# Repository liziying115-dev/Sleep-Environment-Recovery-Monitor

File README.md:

## Sleep Environment & Recovery Monitor
### Project Overview
#### What it does

The Sleep Environment & Recovery Monitor evaluates overnight sleep conditions — light, sound, temperature — and translates them into a simple, physical recovery score visible in the morning. Instead of tracking the body, the system focuses on environmental quality to encourage healthier sleep habits without medical claims.

#### What it looks like

The system consists of two devices:
* A sensor unit placed on a nightstand that quietly monitors the sleep environment overnight (light, sound, temperature)
* A display unit resembling a small alarm clock with an OLED screen, LED indicator, and a stepper-motor-driven gauge needle that physically points to your sleep quality score

### Sensor Device (Sleep Environment Monitor)
#### Description
The sensor device continuously monitors environmental conditions during sleep using a low-power duty cycle. Data is aggregated overnight and transmitted wirelessly to the display device in the morning.

#### Sensors & Parts (part numbers)
| Function | Part Number | Quantity | Description |
|---------|------------|----------|-------------|
| MCU + Wireless| Seeed Studio XIAO ESP32-C3| 1 | BLE, low power |
| Ambient Light Sensor | VEML7700 | 1 | High-sensitivity ambient light sensor (I²C) |
| Microphone | SPH0645LM4H-B | 1 | I²S MEMS microphone, RMS only |
| Temperature | BME280 | 1 | temperature sensing |
| Battery Charger | MCP73831 | 1 | LiPo charging IC |
| LiPo Battery | 3.7V 1000-2000mAh | 1 | Power supply |

#### How it works
- The device wakes on a scheduled interval during sleep hours.
- Light, sound RMS, temperature are sampled.
- Audio is processed locally (no recording or storage).
- All data is time-weighted and stored in local memory.
- At wake time, a summary packet is transmitted to the display device.

### Display Device (Score Interface)
#### Description
The display device receives environmental data wirelessly and presents the overnight Sleep Environment Score using multiple feedback channels: a physical gauge needle, OLED screen, and ambient LED indicator. A single button allows the user to cycle through secondary metrics such as light exposure, noise level, and temperature.

#### Components & Parts
| Function | Part Number | Quantity | Notes |
|---------|------------|----------|------|
| MCU + Wireless | Seeed Studio XIAO ESP32-C3 | 1 | Wireless receiver |
| Display | SSD1306 OLED (128×64) | 1 | Low-power I²C screen |
| Stepper Motor | 28BYJ-48 (5V)        | 1 | Drives gauge needle        |
| Motor Driver  | ULN2003 Driver Board | 1 | Stepper motor driver       |
| Gauge Needle  | Custom (3D printed)  | 1 | Physical pointer (0-100)   |
| LED | Warm White Diffused LED | 1 | Ambient sleep quality indicator |
| Button | Tactile Momentary Switch | 1 | Metric navigation |
| Battery | LiPo 2000 mAh | 1 | Multi-day operation |
| Resistor | 220Ω | 1 | LED current limiting |

#### Gauge Needle Design

Scale: 0-100 (semi-circular arc)

Zones:
- 0-50: Red zone (Poor)
- 50-70: Orange zone (Fair)
- 70-90: Yellow zone (Good)
- 90-100: Green zone (Excellent)

### System Communication & Data Flow

*Figure: Complete data pipeline from sensors through processing to display outputs.*

#### System Communication
The system consists of two standalone devices that communicate wirelessly:

Sensor Unit (Transmitter):
- Operates independently overnight
- Collects and aggregates environmental data
- Transmits single summary packet in the morning

Display Unit (Receiver):
- Listens for BLE transmission from sensor unit
- Receives aggregated data and calculated score
- Updates three output channels: gauge needle, OLED, LED

Communication Protocol:
- Technology: BLE
- Pairing: One-time setup, devices remember each other
- Data Format: JSON or binary packet containing:
  - Overall score (0-100)
  - Average light level (lux)
  - Average sound level (dB RMS)
  - Average temperature (°F/°C)
  - Timestamp

#### Data Flow & Processing Pipeline

During Sleep Period:
1. Sensor device periodically samples ambient light, sound level, and temperature
2. Audio data is processed locally using RMS calculation and basic spectral weighting to emphasize disruptive noise patterns
3. All sensor readings are time-weighted (e.g., disruptions during REM sleep weighted higher)
4. Data is aggregated into a single overnight dataset

Morning Transmission:
1. Aggregated data is converted into a normalized Sleep Environment Score (0-100)
2. Score and detailed metrics are packaged into BLE transmission packet
3. Sensor unit broadcasts packet to display unit
4. Display unit receives data and updates all feedback channels

Physical Feedback:
- Gauge Needle: Stepper motor positions needle to corresponding score (0-100 scale)
- OLED Screen: Displays numeric score and allows cycling through detailed metrics
- LED Indicator: Glows with color corresponding to quality zone (green/yellow/orange/red)

### Future Work
- Optional Wi-Fi connectivity to support long-term data logging or remote visualization

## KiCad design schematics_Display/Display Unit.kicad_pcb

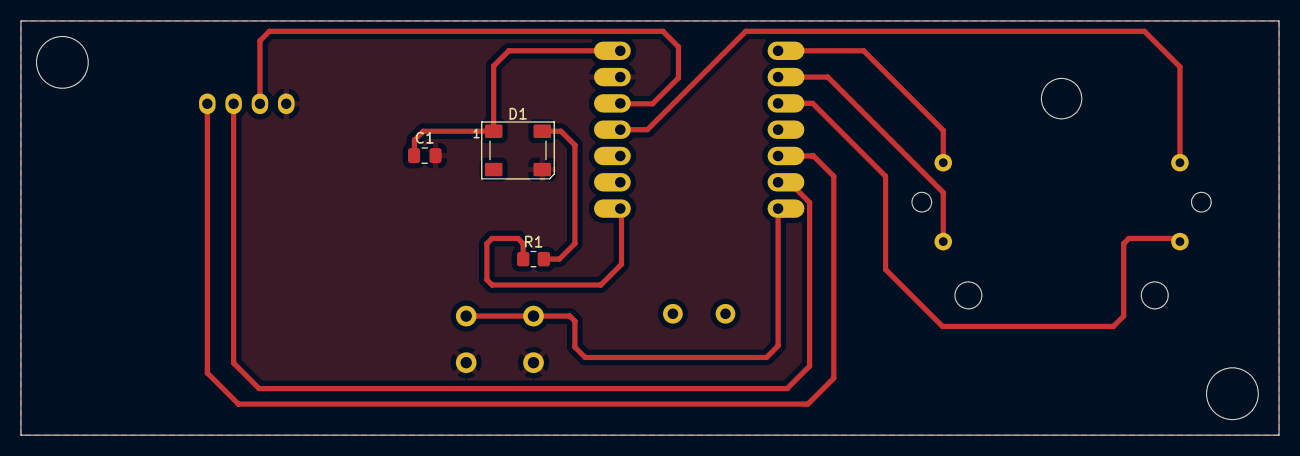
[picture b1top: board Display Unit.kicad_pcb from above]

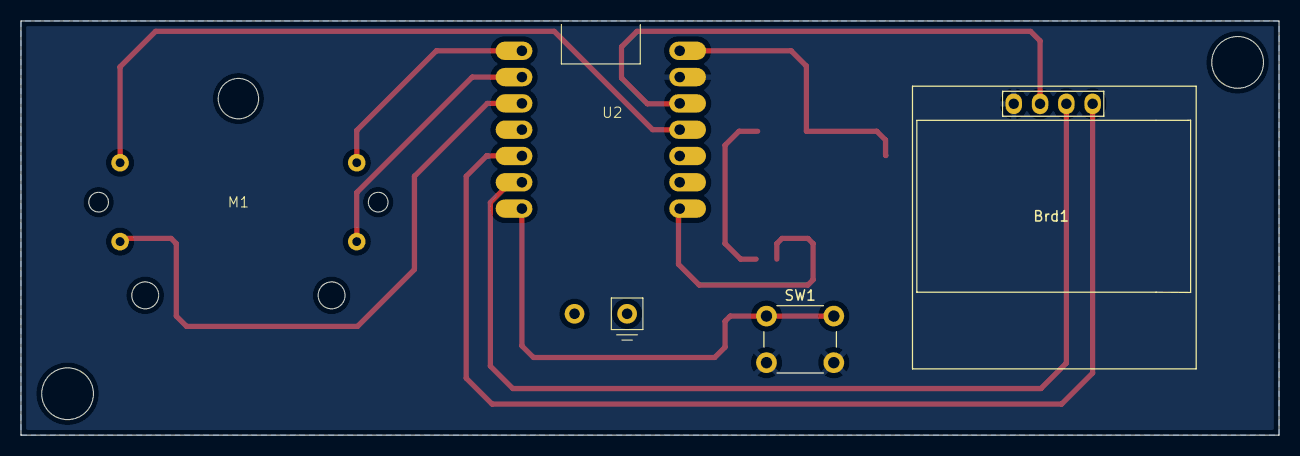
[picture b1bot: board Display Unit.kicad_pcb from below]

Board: 2 copper layers, 121.5 x 40.0 mm, 7 parts (4 on the bottom side), 12 nets.

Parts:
Brd1: SSD1306; 128x64OLED
C1: 100nF; C_0805_2012Metric_Pad1.18x1.45mm_HandSolder
D1: WS2812B; LED_WS2812B_PLCC4_5.0x5.0mm_P3.2mm
M1: Stepper_Motor_bipolar; x27_stepper_two_holes
R1: 33Ω; R_0805_2012Metric_Pad1.20x1.40mm_HandSolder
SW1: SW_Push; SW_PUSH_6mm_H4.3mm
U2: XIAO_ESP32C3; XIAO_ESP32

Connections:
GND: Brd1.1 (GND), C1.2, D1.3 (VSS), SW1.2, U2.13 (GND)
unnamed: Brd1.3 (SCL), U2.6 (GPIO6_A5_D5_SCL)
unnamed: Brd1.4 (SDA), U2.5 (GPIO4_A3_D3_SDA)
unnamed: Brd1.2 (VCC), U2.12 (3V3)
unnamed: D1.4 (DIN), R1.2
unnamed: C1.1, D1.1 (VDD), U2.14 (5V)
unnamed: M1.2 (-), U2.2 (GPIO2_A1_D1)
unnamed: M1.1, U2.1 (GPIO1_A0_D0)
unnamed: M1.4, U2.3 (GPIO3_A2_D2)
unnamed: M1.3, U2.11 (GPIO9_A10_D10_COPI)
unnamed: SW1.1, U2.7 (GPIO43_TX_D6)
unnamed: R1.1, U2.8 (GPIO44_D7_RX)

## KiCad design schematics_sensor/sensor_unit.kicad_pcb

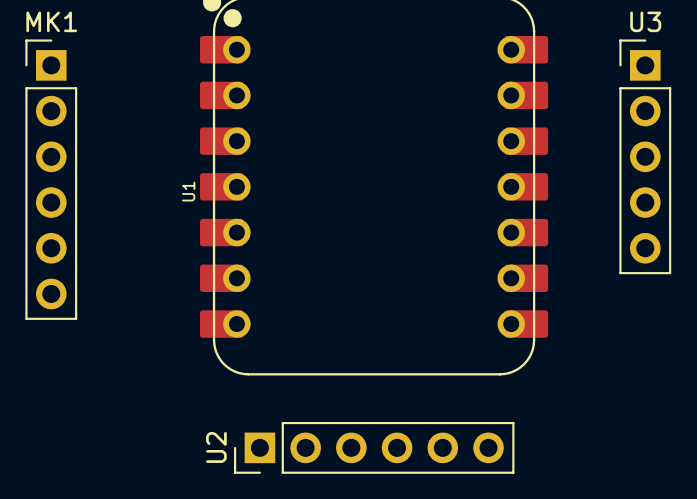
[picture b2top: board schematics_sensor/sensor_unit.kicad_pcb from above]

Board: 2 copper layers, 4 parts (0 on the bottom side), 7 nets, no tracks yet.

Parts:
MK1: SPH0645LM4H; PinHeader_1x06_P2.54mm_Vertical
U1: XIAO ESP32C3; XIAO-ESP32-C3-DIP
U2: BMP280; PinHeader_1x06_P2.54mm_Vertical
U3: VEML7700; PinHeader_1x05_P2.54mm_Vertical

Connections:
unnamed: MK1.5 (3V), U1.12 (3V3), U2.2 (CSB), U2.6 (VDDIO), U3.1 (VIN)
unnamed: MK1.4 (BCLK), U1.2 (GPIO2_A1_D1)
unnamed: MK1.6 (DOUT), U1.3 (GPIO3_A2_D2)
unnamed: MK1.2 (SEL), MK1.3 (GND), U1.13 (GND), U2.1 (GND), U2.5 (SDO), U3.3 (GND)
unnamed: MK1.1 (LRCL), U1.1 (GPIO1_A0_D0)
unnamed: U1.5 (GPIO4_A3_D3_SDA), U2.3 (SDI), U3.5 (SDA)
unnamed: U1.6 (GPIO6_A5_D5_SCL), U2.4 (SCK), U3.4 (SCL)

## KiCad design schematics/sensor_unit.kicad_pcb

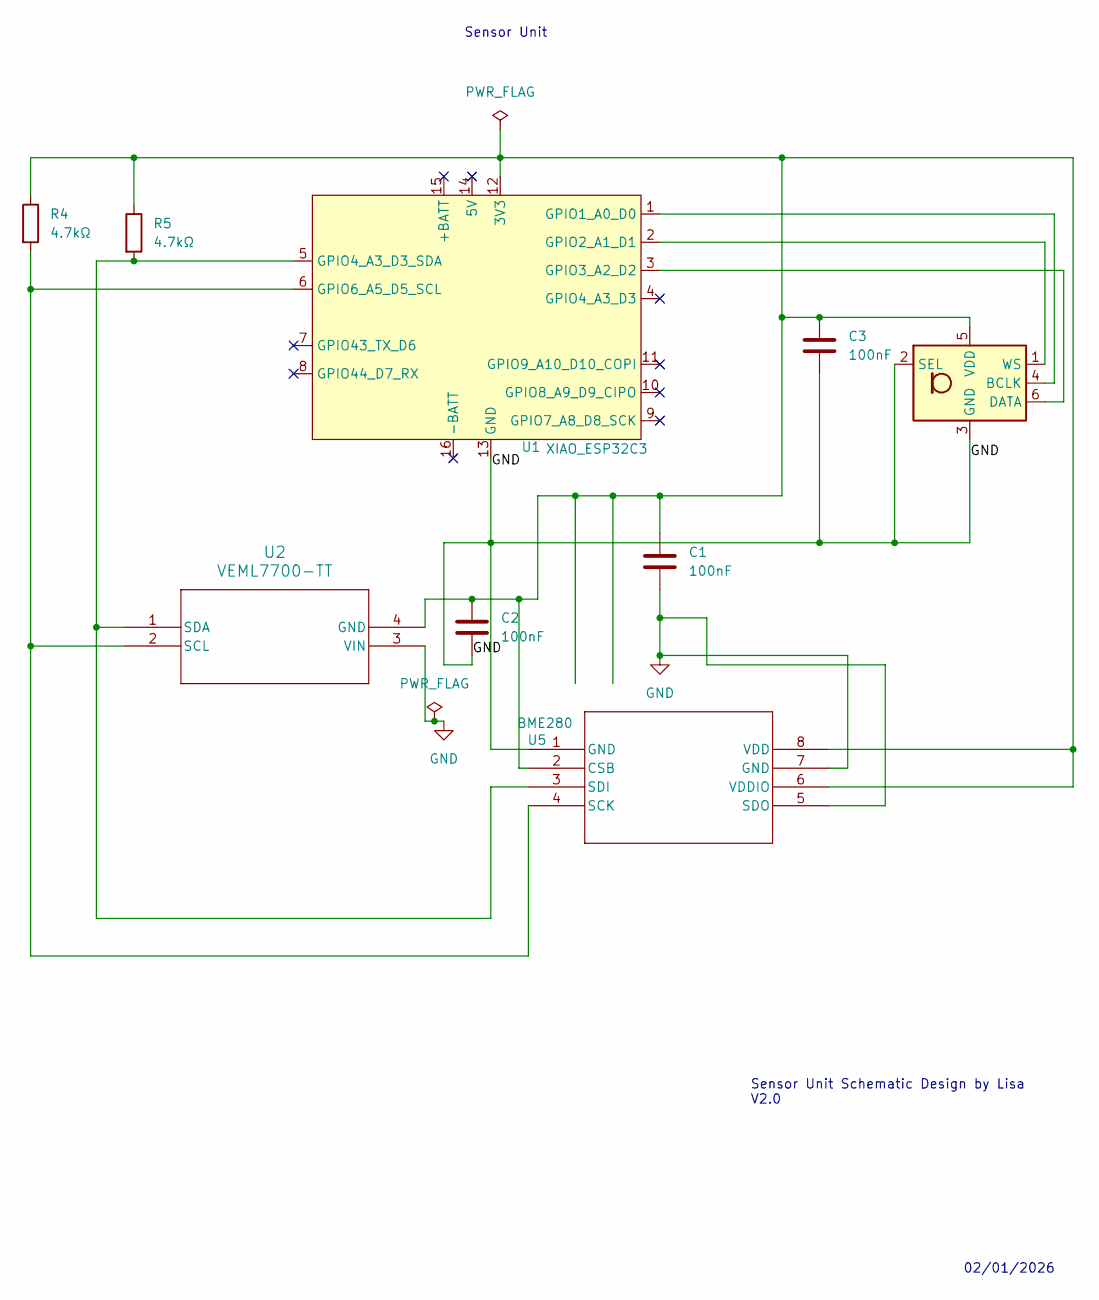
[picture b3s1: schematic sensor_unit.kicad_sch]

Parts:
C1, C2, C3: 100nF; C_0805_2012Metric
MK1: SPH0645LM4H; Knowles_SPH0645LM4H-6_3.5x2.65mm
R4, R5: 4.7kΩ; R_0805_2012Metric
U1: XIAO_ESP32C3; MCU_Seeed_ESP32C3
U2: VEML7700-TT; SMT_L7700-TT_VIS
U5: BME280; DFN8_0p65_2p5SQ_BOS

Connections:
GND: C1.2, C2.2, C3.2, MK1.2 (SEL), MK1.3 (GND), U1.13 (GND), U2.3 (VIN), U5.1 (GND), U5.5 (SDO), U5.7 (GND)
unnamed: MK1.4 (BCLK), U1.1 (GPIO1_A0_D0)
unnamed: MK1.6 (DATA), U1.3 (GPIO3_A2_D2)
unnamed: C1.1, C2.1, C3.1, MK1.5 (VDD), R4.1, R5.1, U1.12 (3V3), U2.4 (GND), U5.2 (CSB), U5.6 (VDDIO), U5.8 (VDD)
unnamed: MK1.1 (WS), U1.2 (GPIO2_A1_D1)
unnamed: R5.2, U1.5 (GPIO4_A3_D3_SDA), U2.1 (SDA), U5.3 (SDI)
unnamed: R4.2, U1.6 (GPIO6_A5_D5_SCL), U2.2 (SCL), U5.4 (SCK)

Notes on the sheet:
Sensor Unit
Sensor Unit Schematic Design by Lisa V2.0
02/01/2026

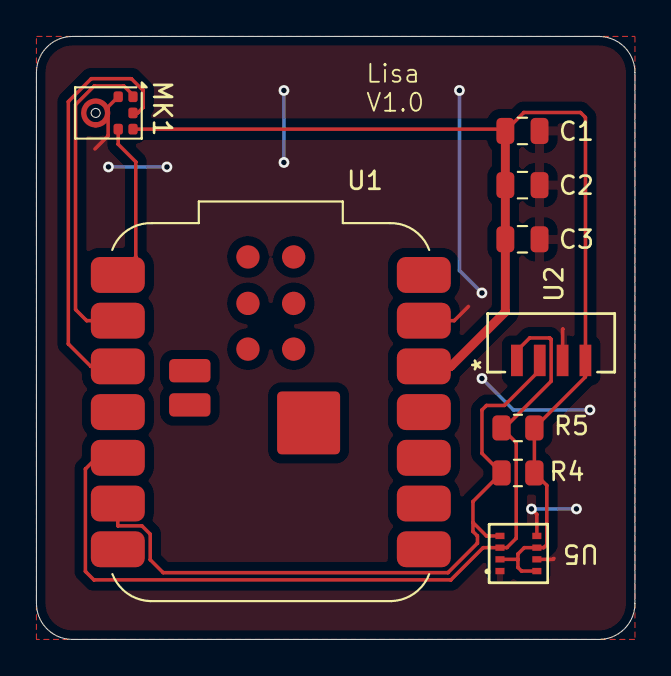
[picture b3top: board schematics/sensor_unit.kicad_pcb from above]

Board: 2 copper layers, 33.2 x 33.5 mm, 9 parts (0 on the bottom side), 7 nets.

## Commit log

2026-01-19 add README with data flow diagram and corrections
2026-01-19 add datasheet and revised tables
2026-01-19 add quantity column to component tables
2026-01-20 Add detailed device sketches
2026-01-20 Update README with sketches
2026-01-20 Add commit history screenshot
2026-01-25 Add stepper motor gauge needle and update system architecture
2026-01-25 Add readme
2026-01-26 edit components
2026-01-27 add schematics
2026-01-27 add bom
2026-02-08 Power model
2026-03-01 Add sensor unit test coed
2026-03-16 add coding, pcb, and revised sketches
